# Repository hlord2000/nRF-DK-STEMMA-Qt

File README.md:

# New nRF-DK STEMMA-QT/Qwiic Fin

Serves as an example of the new nRF devkit pinout.

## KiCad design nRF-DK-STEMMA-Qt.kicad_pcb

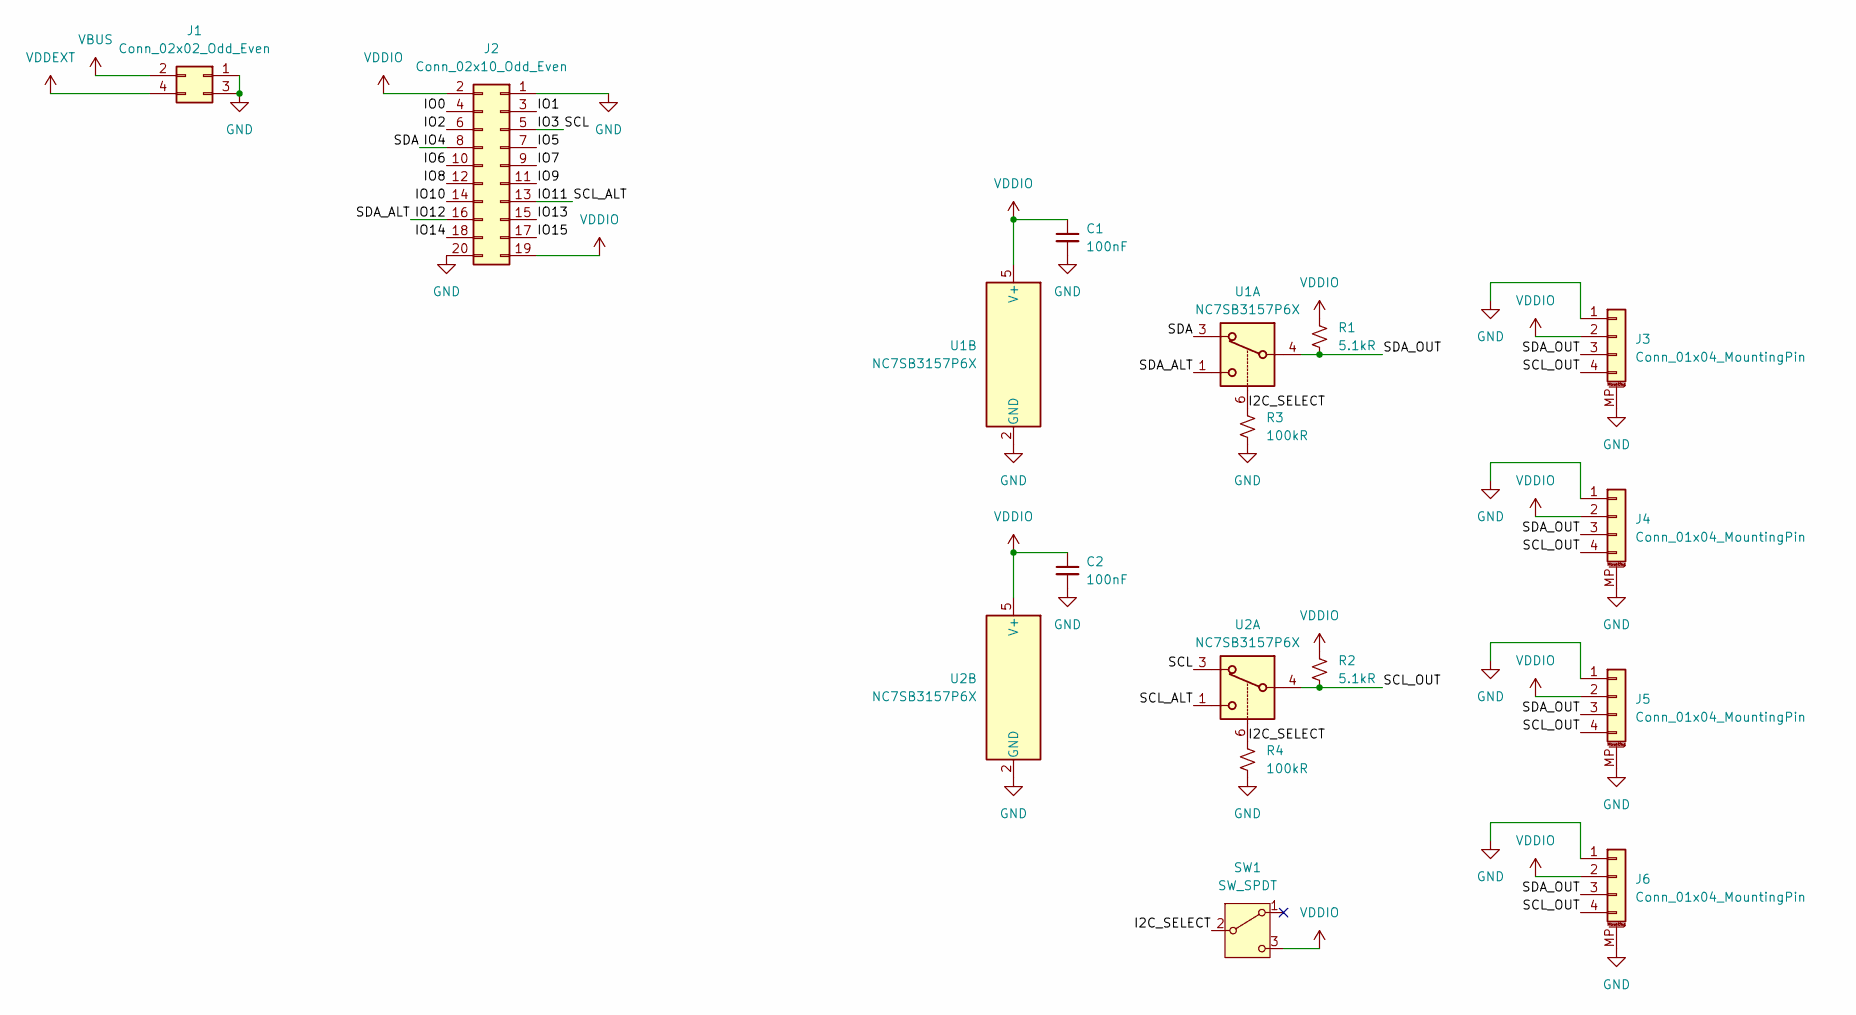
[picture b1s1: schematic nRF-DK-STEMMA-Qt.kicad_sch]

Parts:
C1, C2: 100nF; C_0402_1005Metric
J1: Conn_02x02_Odd_Even; PinSocket_2x02_P2.54mm_Horizontal
J2: Conn_02x10_Odd_Even; PinSocket_2x10_P2.54mm_Horizontal
J3, J4, J5, J6: Conn_01x04_MountingPin; JST_SH_SM04B-SRSS-TB_1x04-1MP_P1.00mm_Horizontal
R1, R2: 5.1kR; R_0402_1005Metric
R3, R4: 100kR; R_0402_1005Metric
SW1: SW_SPDT; SW_SPDT_PCM12
U1, U2: NC7SB3157P6X; SOT-363_SC-70-6

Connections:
/I2C_SELECT: R3.1, R4.1, SW1.2 (B), U1.6, U2.6
/IO0: J2.4
/IO1: J2.3
/IO2: J2.6
/IO3: J2.5, U2.3
/IO4: J2.8, U1.3
/IO5: J2.7
/IO6: J2.10
/IO7: J2.9
/IO8: J2.12
/IO9: J2.11
/IO10: J2.14
/IO11: J2.13, U2.1
/IO12: J2.16, U1.1
/IO13: J2.15
/IO14: J2.18
/IO15: J2.17
/SCL_OUT: J3.4, J4.4, J5.4, J6.4, R2.2, U2.4
/SDA_OUT: J3.3, J4.3, J5.3, J6.3, R1.2, U1.4
GND: C1.2, C2.2, J1.1, J1.3, J2.1, J2.20, J3.1, J3.MP (MountPin), J4.1, J4.MP (MountPin), J5.1, J5.MP (MountPin), J6.1, J6.MP (MountPin), R3.2, R4.2, U1.2 (GND), U2.2 (GND)
VBUS: J1.2
VDDEXT: J1.4
VDDIO: C1.1, C2.1, J2.2, J2.19, J3.2, J4.2, J5.2, J6.2, R1.1, R2.1, SW1.3 (C), U1.5 (V+), U2.5 (V+)

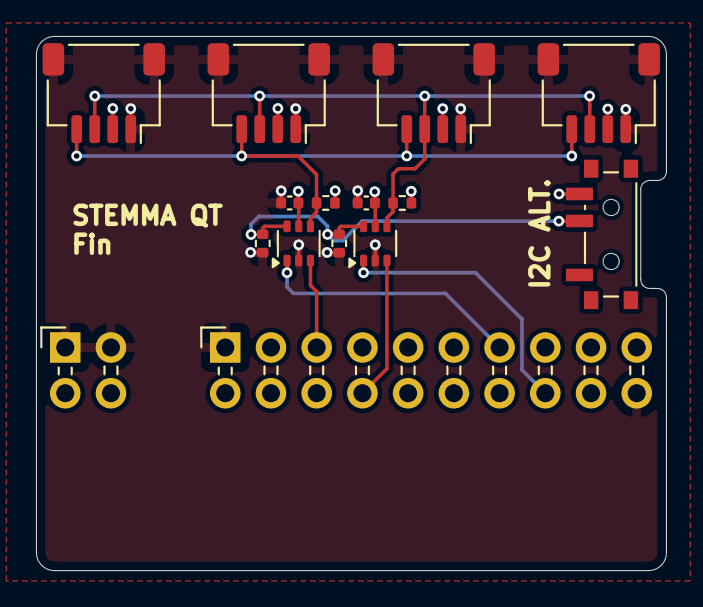
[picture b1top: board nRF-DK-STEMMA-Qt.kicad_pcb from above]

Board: 4 copper layers, 35.0 x 29.7 mm, 15 parts (0 on the bottom side), 9 nets.

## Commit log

2024-12-23 Initial commit.
